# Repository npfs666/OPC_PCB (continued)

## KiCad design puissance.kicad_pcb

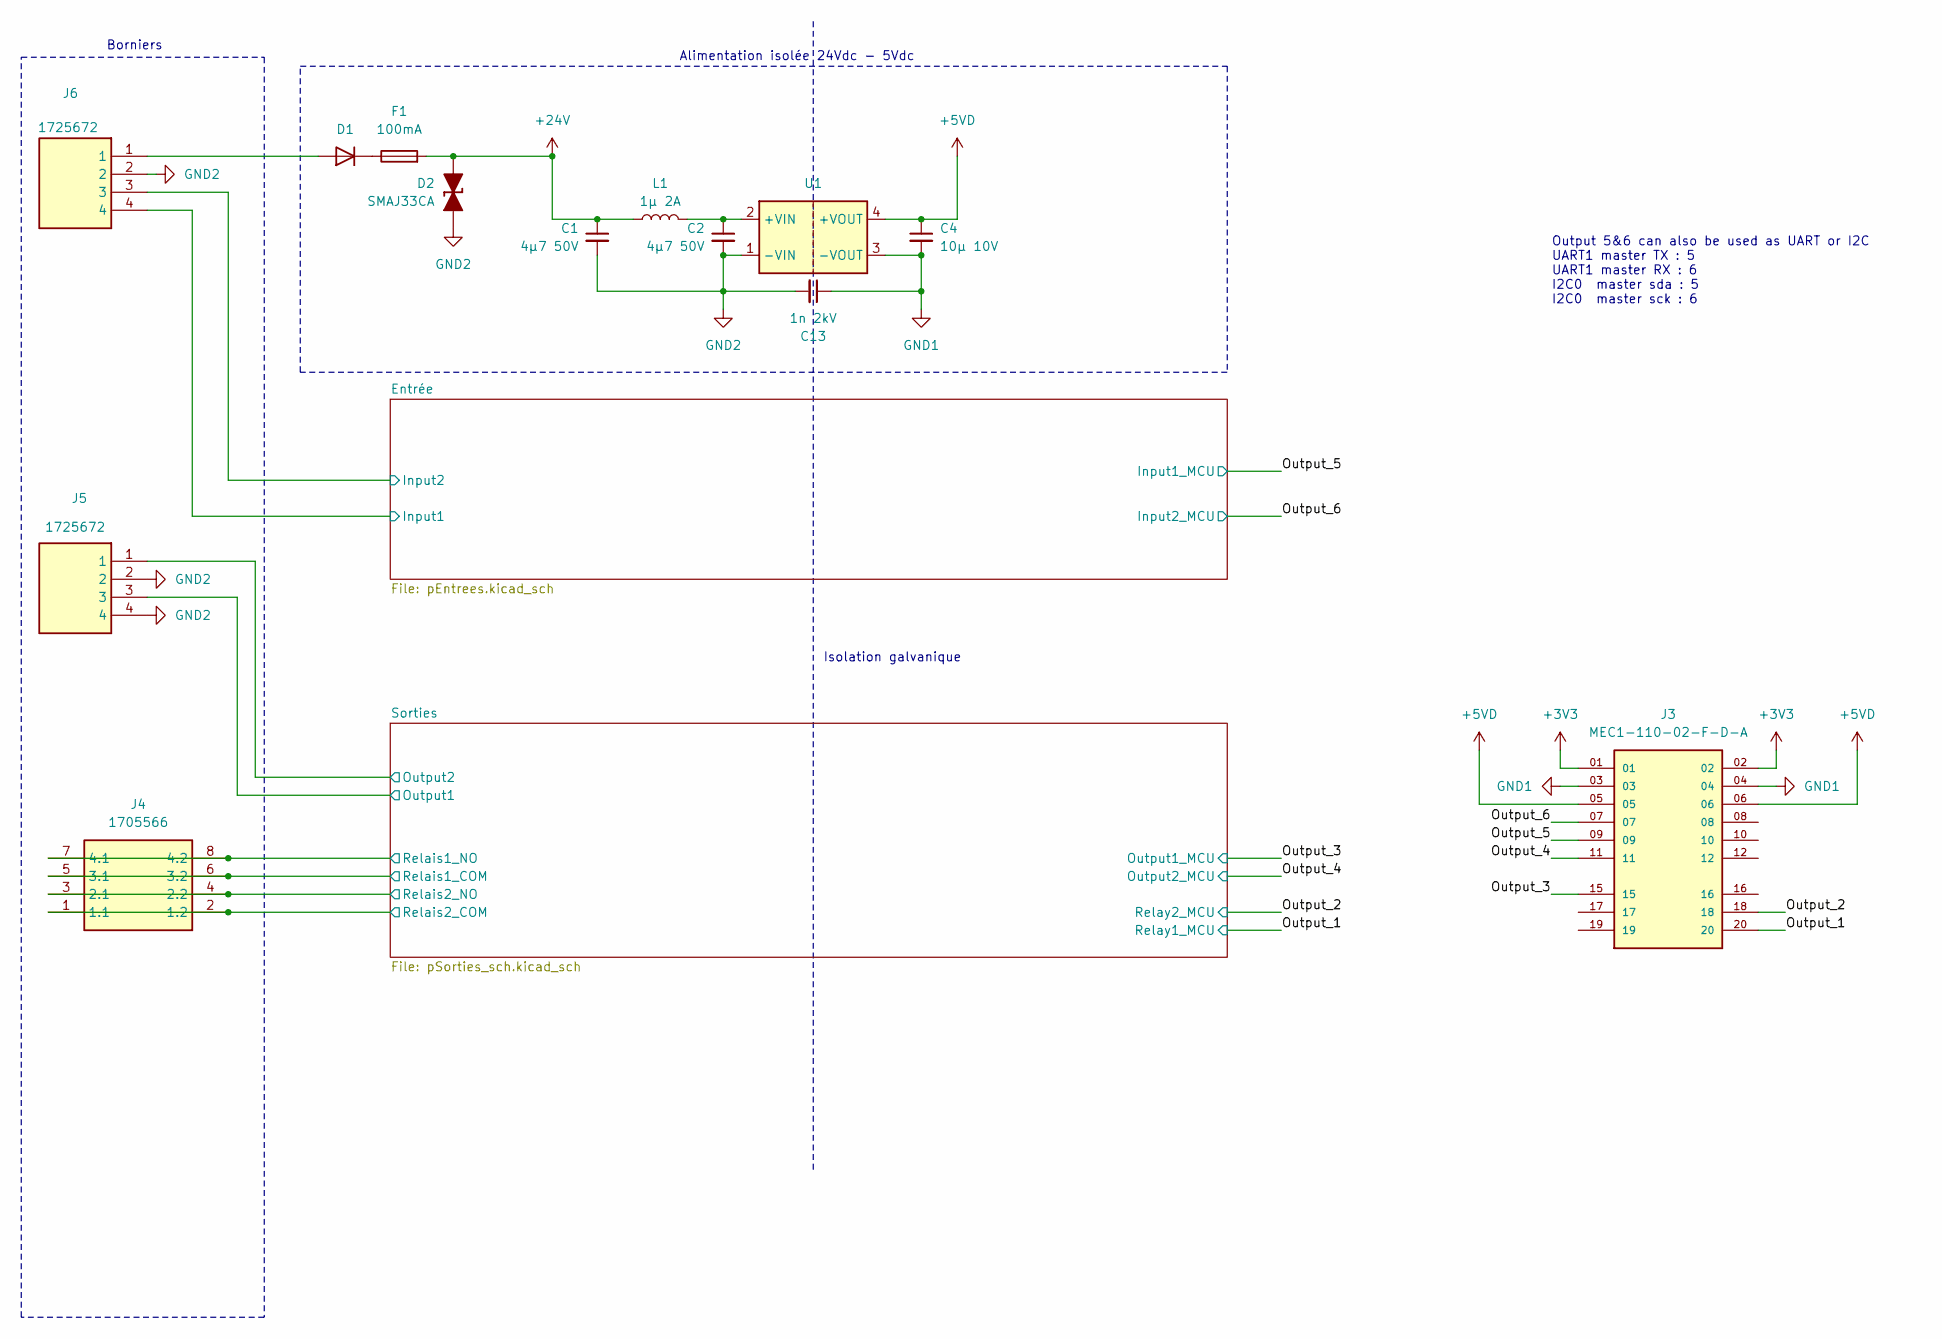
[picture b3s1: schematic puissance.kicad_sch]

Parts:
C1, C2: 4µ7 50V; C_1206_3216Metric; MPN GRM319R61H475KA12D; LCSC Part # C29823
C4: 10µ 10V; C_0603_1608Metric_Pad1.08x0.95mm_HandSolder; MPN GRM188R61A106ME69D; LCSC Part # C19702
C13: 1n 2kV; C_1206_3216Metric; MPN 885342208024; LCSC Part # C9196
D1: FR1G; D_SMA; MPN FR1G; LCSC Part # C412437
D2: SMAJ33CA; D_SMA_TVS; MPN 824501331
F1: 100mA; Fuse_1210_3225Metric; MPN 0ZCH0010FF2E
J3: MEC1-110-02-F-D-A; MEC1-110-02-F-D-A-MALE
J4: 1705566; Manufacturer_Part_Number 1705566; Mouser Part Number 651-1705566
J5, J6: 1725672; Manufacturer_Part_Number 1725672; Mouser Part Number 651-1725672
L1: 1µ 2A; L_1008_2520Metric; MPN MAMK2520T1R0M; LCSC Part # C162587
U1: 1779205311; U_Wurth_WPME-FISM-SIP-4_1779205311; Part Number 1779205311; LCSC Part # C6652237

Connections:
+3V3: J3.01, J3.02; also elsewhere on the board
+5VD: C4.1, J3.05, J3.06, U1.4 (+VOUT)
+24V: C1.1, D2.1 (K), F1.2, L1.1; also elsewhere on the board
/Entrée/Input1: J6.4; also elsewhere on the board
/Entrée/Input2: J6.3; also elsewhere on the board
/Output_1: J3.20; also elsewhere on the board
/Output_2: J3.18; also elsewhere on the board
/Output_3: J3.15; also elsewhere on the board
/Output_4: J3.11; also elsewhere on the board
/Output_5: J3.09; also elsewhere on the board
/Output_6: J3.07; also elsewhere on the board
/Sorties/Output1: J5.3; also elsewhere on the board
/Sorties/Output2: J5.1; also elsewhere on the board
/Sorties/Relais1_COM: J4.5 (3.1), J4.6 (3.2); also elsewhere on the board
/Sorties/Relais1_NO: J4.7 (4.1), J4.8 (4.2); also elsewhere on the board
/Sorties/Relais2_COM: J4.1 (1.1), J4.2 (1.2); also elsewhere on the board
/Sorties/Relais2_NO: J4.3 (2.1), J4.4 (2.2); also elsewhere on the board
GND1: C4.2, C13.1, J3.03, J3.04, U1.3 (-VOUT); also elsewhere on the board
GND2: C1.2, C2.2, C13.2, D2.2 (A), J5.2, J5.4, J6.2, U1.1 (-VIN); also elsewhere on the board
unnamed: D1.2 (A), J6.1
unnamed: D1.1 (K), F1.1
unnamed: C2.1, L1.2, U1.2 (+VIN)

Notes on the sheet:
Borniers
Output 5&6 can also be used as UART or I2C UART1 master TX : 5 UART1 master RX : 6 I2C0 master sda : 5 I2C0 master sck : 6
Isolation galvanique
Alimentation isolée 24Vdc - 5Vdc

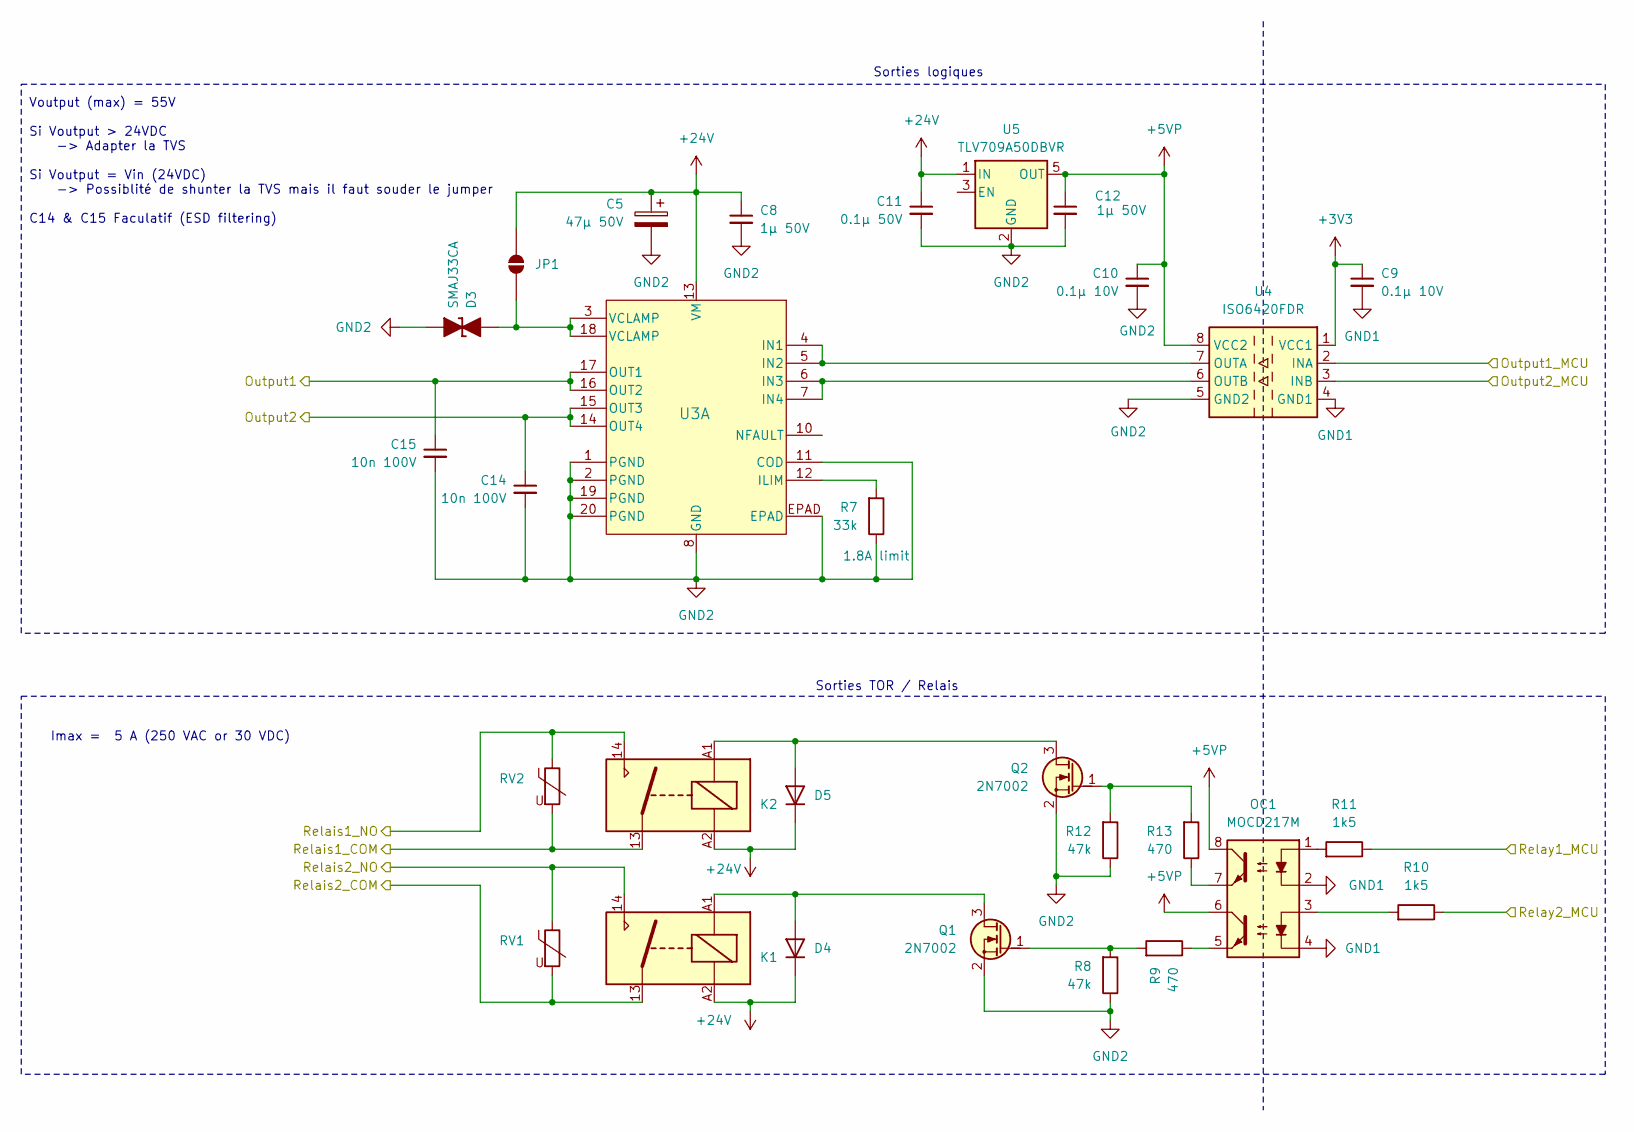
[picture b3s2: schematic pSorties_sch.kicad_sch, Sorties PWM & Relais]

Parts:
C5: 47µ 50V; CP_Elec_6.3x7.7; MPN 865080645012; LCSC Part # C72523
C8, C12: 1µ 50V; C_0805_2012Metric_Pad1.18x1.45mm_HandSolder; MPN GRM219R61H105MA73D; LCSC Part # C28323
C9, C10: 0.1µ 10V; C_0603_1608Metric_Pad1.08x0.95mm_HandSolder; MPN 885012206020; LCSC Part # C14663
C11: 0.1µ 50V; C_0603_1608Metric_Pad1.08x0.95mm_HandSolder; MPN GCM188L81H104MA57D; LCSC Part # C14663
C14, C15: 10n 100V; C_0603_1608Metric_Pad1.08x0.95mm_HandSolder; MPN GRM188R72A103MA01J; LCSC Part # C57112
D3: SMAJ33CA; D_SMA_TVS; MPN 824501331
D4, D5: FR1G; D_SMA; MPN FR1G; LCSC Part # C412437
JP1: SolderJumper_2_Open; SolderJumper-2_P1.3mm_Open_RoundedPad1.0x1.5mm
K1, K2: G6DN-1A-L DC24; G6DN; MPN G6DN-1A-L DC24
OC1: MOCD217M; SO-8_3.9x6.2mm_P1.27mm; MPN MOCD217M; LCSC Part # C258262
Q1, Q2: 2N7002; SOT-23; MPN T2N7002BK,LM; LCSC Part # C8545
R7: 33k; R_0603_1608Metric_Pad0.98x0.95mm_HandSolder; MPN ERJ-3GEYJ333V; LCSC Part # C4216
R8, R12: 47k; R_0603_1608Metric_Pad0.98x0.95mm_HandSolder; MPN ERJ-3GEYJ473V; LCSC Part # C25819
R9, R13: 470; R_0603_1608Metric_Pad0.98x0.95mm_HandSolder; MPN ERJ-3GEYJ470V; LCSC Part # C23179
R10, R11: 1k5; R_0603_1608Metric_Pad0.98x0.95mm_HandSolder; MPN ERJ-3GEYJ152V; LCSC Part # C22843
RV1, RV2: MOV-07D391KKTR; RV_Disc_D9mm_W3.9mm_P5mm; MPN MOV-07D391KKTR
U3: DRV81545PWPR; U_TSSOP_PWP0020AC_TEX; MPN DRV81545PWPR; LCSC Part # C53201928
U4: ISO6420FDR; SOIC-8_3.9x4.9mm_P1.27mm; MPN ISO6420FDR
U5: TLV709A50DBVR; SOT-23-5; MPN TLV709A50DBVR

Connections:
+3V3: C9.1, U4.1 (VCC1); also elsewhere on the board
+5VP: C10.1, C12.1, OC1.6, OC1.8, U4.8 (VCC2), U5.5 (OUT)
+24V: C5.1, C8.1, C11.1, D4.1 (K), D5.1 (K), JP1.2 (B), K1.A2, K2.A2, U3.13 (VM), U5.1 (IN); also elsewhere on the board
/Output_1: R11.1; also elsewhere on the board
/Output_2: R10.1; also elsewhere on the board
/Output_3: U4.2 (INA); also elsewhere on the board
/Output_4: U4.3 (INB); also elsewhere on the board
/Sorties/Output1: C15.1, U3.16 (OUT2), U3.17 (OUT1); also elsewhere on the board
/Sorties/Output2: C14.1, U3.14 (OUT4), U3.15 (OUT3); also elsewhere on the board
/Sorties/Relais1_COM: K2.13, RV2.2; also elsewhere on the board
/Sorties/Relais1_NO: K2.14, RV2.1; also elsewhere on the board
/Sorties/Relais2_COM: K1.13, RV1.2; also elsewhere on the board
/Sorties/Relais2_NO: K1.14, RV1.1; also elsewhere on the board
GND1: C9.2, OC1.2, OC1.4, U4.4 (GND1); also elsewhere on the board
GND2: C5.2, C8.2, C10.2, C11.2, C12.2, C14.2, C15.2, D3.2 (A), Q1.2 (S), Q2.2 (S), R7.1, R8.1, R12.1, U3.1 (PGND), U3.2 (PGND), U3.8 (GND), U3.11 (COD), U3.19 (PGND), U3.20 (PGND), U3.EPAD, U4.5 (GND2), U5.2 (GND); also elsewhere on the board
unnamed: D3.1 (K), JP1.1 (A), U3.3 (VCLAMP), U3.18 (VCLAMP)
unnamed: D4.2 (A), K1.A1, Q1.3 (D)
unnamed: D5.2 (A), K2.A1, Q2.3 (D)
unnamed: OC1.1, R11.2
unnamed: OC1.3, R10.2
unnamed: OC1.5, R9.1
unnamed: OC1.7, R13.1
unnamed: Q1.1 (G), R8.2, R9.2
unnamed: Q2.1 (G), R12.2, R13.2
unnamed: R7.2, U3.12 (ILIM)
unnamed: U3.4 (IN1), U3.5 (IN2), U4.7 (OUTA)
unnamed: U3.6 (IN3), U3.7 (IN4), U4.6 (OUTB)

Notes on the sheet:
Sorties TOR / Relais
Voutput (max) = 55V Si Voutput > 24VDC -> Adapter la TVS Si Voutput = Vin (24VDC) -> Possiblité de shunter la TVS mais il faut souder le jumper C14 & C15 Faculatif (ESD filtering)
Imax = 5 A (250 VAC or 30 VDC)
Sorties logiques

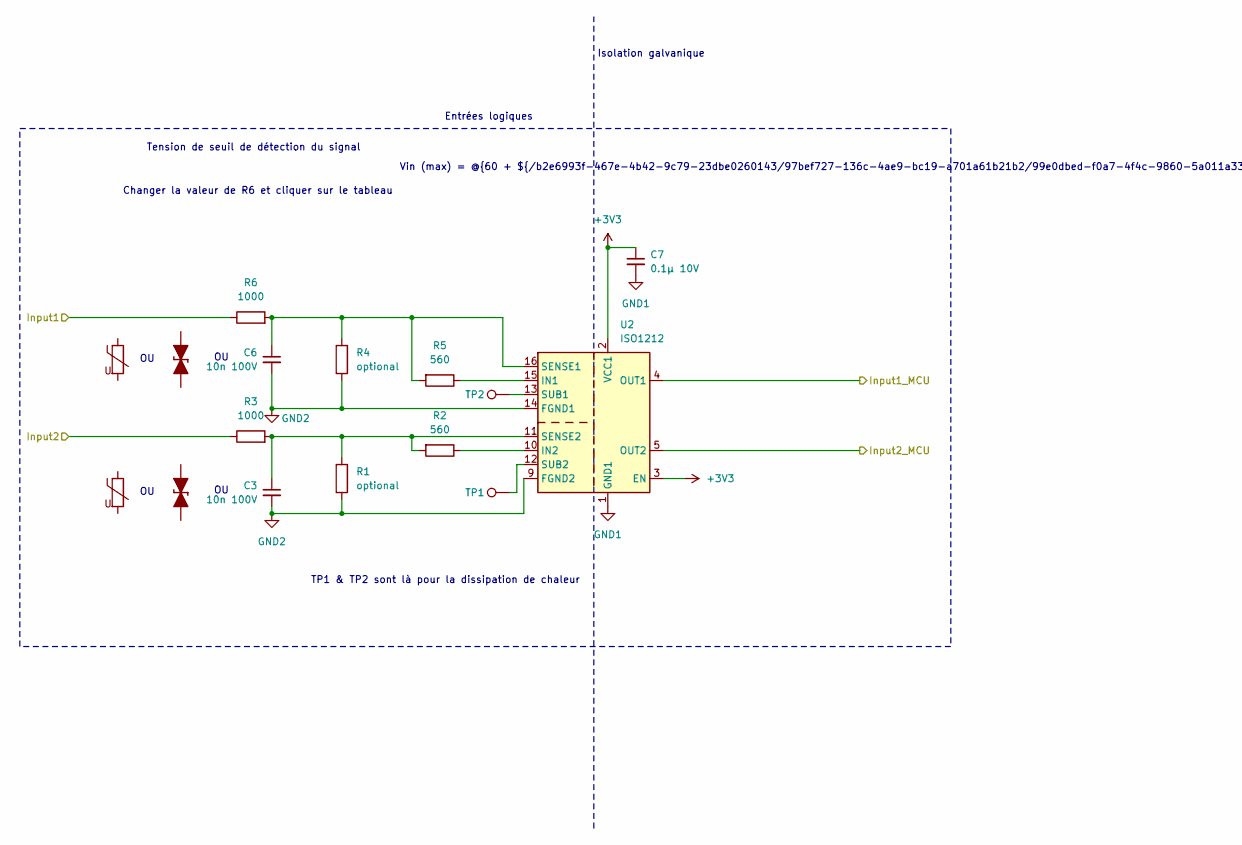
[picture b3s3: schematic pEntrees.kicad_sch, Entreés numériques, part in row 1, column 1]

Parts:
C3, C6: 10n 100V; C_0603_1608Metric; MPN GRM188R72A103MA01J; LCSC Part # C57112
C7: 0.1µ 10V; C_0603_1608Metric_Pad1.08x0.95mm_HandSolder; MPN 885012206020; LCSC Part # C14663
D10, D11: (no value)
R1, R4: optional; R_0805_2012Metric_Pad1.20x1.40mm_HandSolder
R2, R5: 560; R_0603_1608Metric; MPN ERJ-3GEYJ560V; LCSC Part # C23204
R3, R6: 1000; R_1206_3216Metric; MPN ERJ-6GEYJ242V; LCSC Part # C4410
RV10, RV11: Varistor
TP1, TP2: TestPoint; TestPoint_Pad_2.0x2.0mm
U2: ISO1212; SSOP-16_3.9x4.9mm_P0.635mm; MPN ISO1212DBQR

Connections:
+3V3: C7.1, U2.2 (VCC1), U2.3 (EN); also elsewhere on the board
/Entrée/Input1: R6.1; also elsewhere on the board
/Entrée/Input2: R3.1; also elsewhere on the board
/Output_5: U2.4 (OUT1); also elsewhere on the board
/Output_6: U2.5 (OUT2); also elsewhere on the board
GND1: C7.2, U2.1 (GND1), U2.8 (GND1); also elsewhere on the board
GND2: C3.2, C6.2, R1.1, R4.1, U2.9 (FGND2), U2.14 (FGND1); also elsewhere on the board
unnamed: R5.1, U2.15 (IN1)
unnamed: R2.1, U2.10 (IN2)
unnamed: C6.1, R4.2, R5.2, R6.2, U2.16 (SENSE1)
unnamed: C3.1, R1.2, R2.2, R3.2, U2.11 (SENSE2)
unnamed: TP2.1 (1_1), U2.13 (SUB1)
unnamed: TP1.1 (1_1), U2.12 (SUB2)

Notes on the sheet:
Vin (max) = @{60 + ${/b2e6993f-467e-4b42-9c79-23dbe0260143/97bef727-136c-4ae9-bc19-a701a61b21b2/99e0dbed-f0a7-4f4c-9860-5a011a33f80f:VALUE} * 0.0021 * 562 / ${/b2e6993f-467e-4b42-9c79-23dbe0260143/97bef727-136c-4ae9-bc19-a701a61b21b2/c8e65150-a29e-4934-ab6e-f5d5b94ba4d4:VALUE}}V
Tension de seuil de détection du signal
TP1 & TP2 sont là pour la dissipation de chaleur
Changer la valeur de R6 et cliquer sur le tableau
Isolation galvanique
Entrées logiques

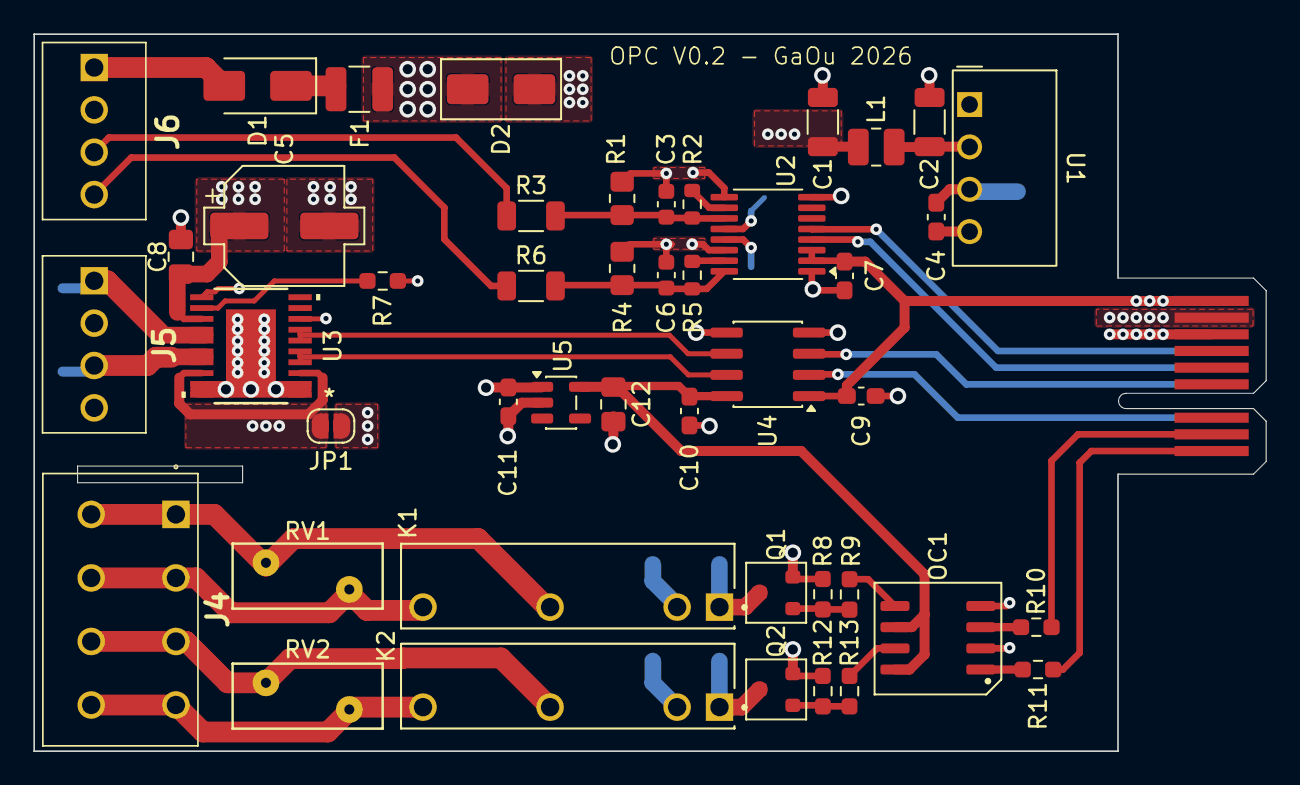
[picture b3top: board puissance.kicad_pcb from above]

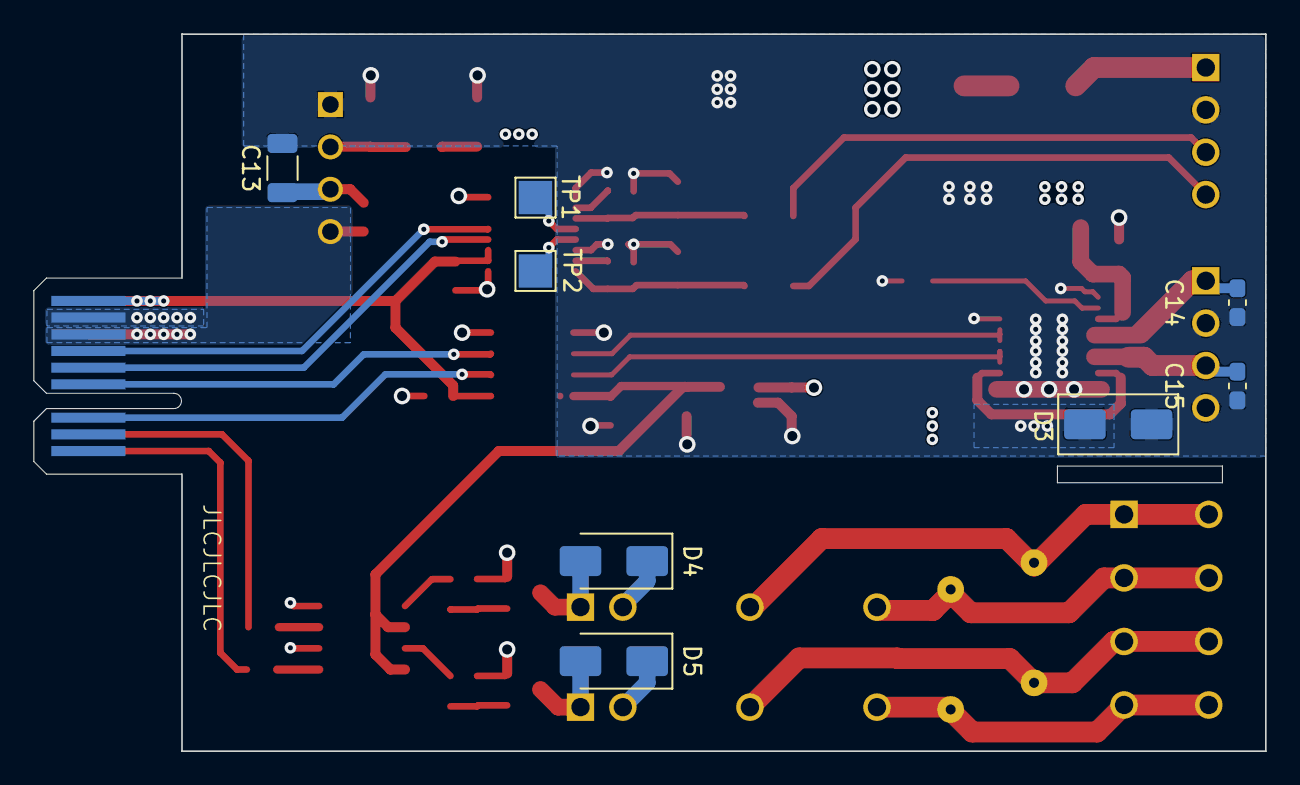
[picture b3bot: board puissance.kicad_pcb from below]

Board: 4 copper layers, 73.9 x 43.0 mm, 54 parts (9 on the bottom side), 41 nets.

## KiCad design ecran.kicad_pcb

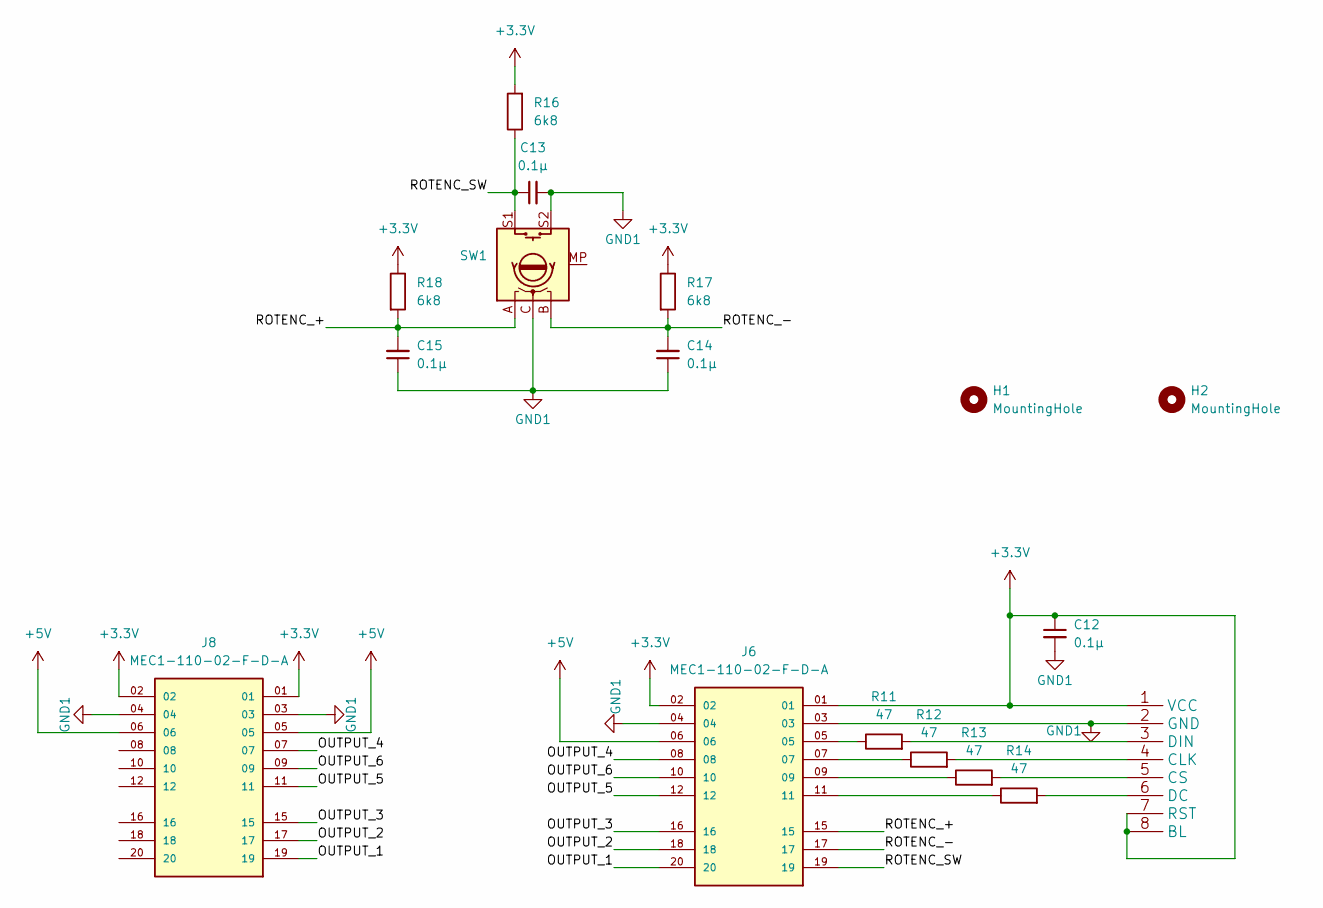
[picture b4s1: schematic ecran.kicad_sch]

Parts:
C12, C13, C14, C15: 0.1µ; C_0603_1608Metric_Pad1.08x0.95mm_HandSolder; LCSC Part # C14663
H1, H2: MountingHole; MountingHole_3.2mm_M3_DIN965
J6, J8: MEC1-110-02-F-D-A; SAMTEC_MEC1-110-02-F-D-A
R11, R12, R13, R14: 47; R_0603_1608Metric_Pad0.98x0.95mm_HandSolder; LCSC Part # C23182
R16, R17, R18: 6k8; R_0603_1608Metric_Pad0.98x0.95mm_HandSolder; LCSC Part # C23212
SW1: RotaryEncoder_Switch_MP; RotaryEncoder_Alps_EC11E-Switch_Vertical_H20mm_MountingHoles
U8: WAVESHARE-1.14-LCD-2

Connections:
+5V: J6.06, J8.05, J8.06
/LCD_CLK: J6.07, R12.1
/LCD_CS: J6.09, R13.1
/LCD_DC: J6.11, R14.1
/LCD_DIN: J6.05, R11.1
/OUTPUT_1: J6.20, J8.19, J8.20
/OUTPUT_2: J6.18, J8.17, J8.18
/OUTPUT_3: J6.16, J8.15, J8.16
/OUTPUT_4: J6.08, J8.07, J8.08
/OUTPUT_5: J6.12, J8.11, J8.12
/OUTPUT_6: J6.10, J8.09, J8.10
/ROTENC_+: C15.2, J6.15, R18.2, SW1.A
/ROTENC_-: C14.2, J6.17, R17.2, SW1.B
/ROTENC_SW: C13.1, J6.19, R16.1, SW1.S1
unnamed: R12.2, U8.4 (CLK)
unnamed: R13.2, U8.5 (CS)
unnamed: R14.2, U8.6 (DC)
unnamed: R11.2, U8.3 (DIN)

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
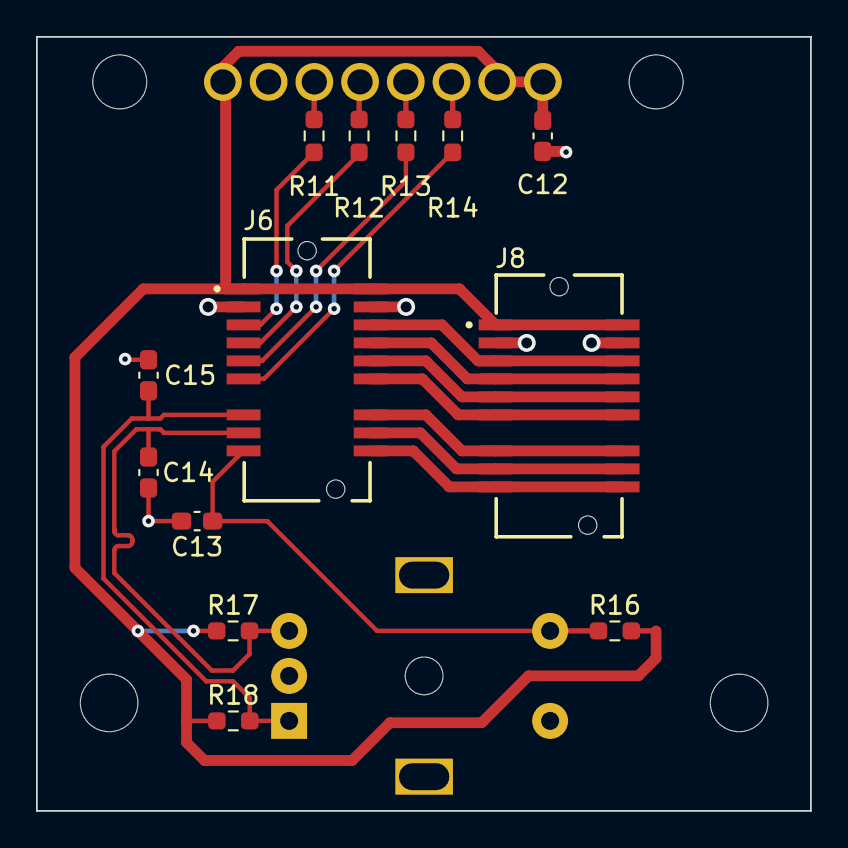
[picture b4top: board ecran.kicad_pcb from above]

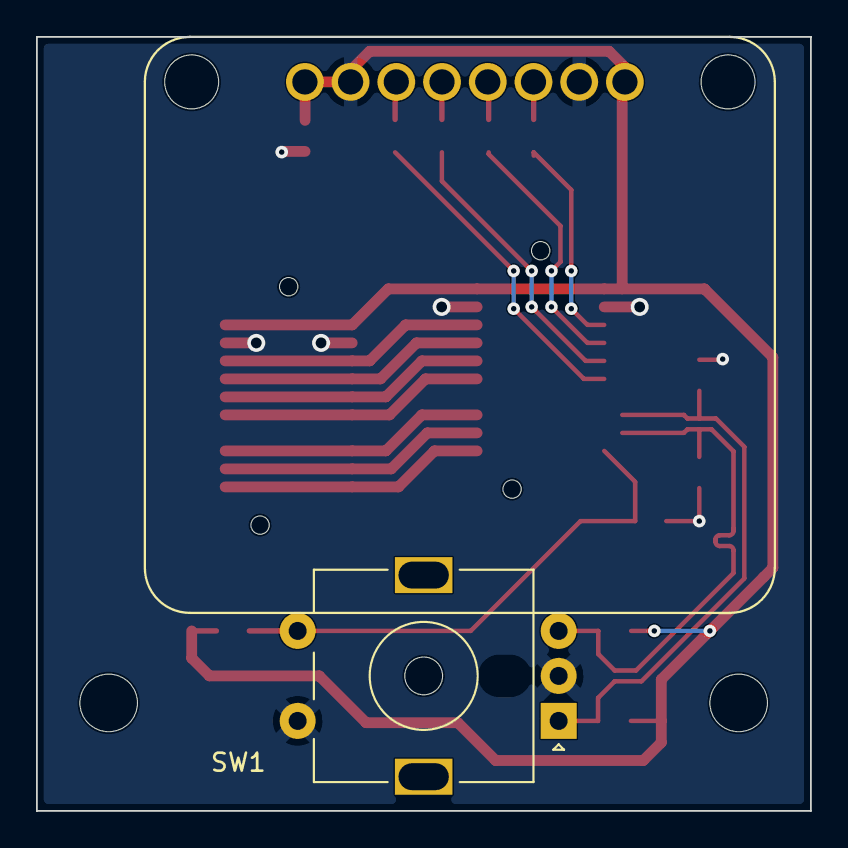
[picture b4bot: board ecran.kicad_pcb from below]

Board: 2 copper layers, 43.0 x 43.0 mm, 17 parts (2 on the bottom side), 20 nets.
